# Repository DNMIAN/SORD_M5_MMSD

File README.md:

SORD m5 メモリマッパー (+SD)  

注意  
・m5 Jr.に挿せるかは検証できていません。  
・純正電源で動作するかは確認できていません。（外部電源入力は可能）  

1. 概要  
  
本ハードウェアは、SORD m5（および互換PC）に、ROMを512Kバイト、RAMを512Kバイトを拡張する装置です。  
各メモリは16Kバイト単位のセグメントに分割され、ROM32ページ、RAM32ページとして管理します。  
CPUのメモリ空間64Kバイトを16Kバイト単位で4分割し、CPU空間0～3とします。  
それぞれのCPU空間について、任意のページを対応させることができます。  
（いわゆるMSXのメモリマッパーです）  
  
また、yanatakaさんのMSX_SD ver1.6 (https://github.com/yanataka60/MSX_SD) を使用することを目的とした、  
MSXカートリッジI/F（以降、MSX-I/F)を備えています。  

2. 製作について  
  
組み立て以外に、EPROM書き込みが必要です。  
  
また、MSX_SDのドキュメントも必ず読みましょう。  
MSX_SDはArduinoスケッチ書き込みが必要です。  

3. 基板、部品リスト  
  
回路図とガーバーデータはKiCad7.0で作成しています。  
  
動作確認をした部品リストを、以下に示します。  
74HCをLSにした場合、動作しない可能性があります。  
  
U1,U2 : 74LS670 x2  
U3 : 74HC244  
U4 : HM628512ALP-7  
U5 : 512Kx8bit以下 DIP32 EPROM（M27C4001-10F1,W27C010-70で確認）  
U6 : 74HC20  
U7 : 74HC00  
U8 : 74HC30  
U9 : 74HC139  
CON : カードエッジコネクタ 2x25P 2.54mm  
C1～C9 : 積層セラミックコンデンサ 50V 0.1uF x9  
C10 : 電解コンデンサ 16V 100uF  
RN1 : 集合抵抗 6素子 10kΩ  
R1 : 抵抗 10kΩ  
SW1,SW2 : タクトスイッチ TVDP17-050B-D x2  
EX5V : ピンヘッダ 1x2P 2.54mm  
EX12V,GND : ピンヘッダ 1x3P 2.54mm  
EXIO,A4～A7 : ピンヘッダ 1x3P 2.54mm x5  
ICソケット : DIP32（U5用）  
ジャンパーピン : 2.54mm（EX5V,EXIO,A4～A7用） x6  
  
MSX_SD ver1.6 : 基板は公開されているガーバーから作成  
U1 : 74HC02  
U2 : 74HC138  
U3 : W27C512-45Z（後半32KBを使用） ※MSXで動作確認時に使用  
U4 : uPD8255AC-5  
U5 : Arduino Pro Mini 328 5V 16MHz（ピンヘッダ付属）  
J3 : MicroSD Card Adapter  
C1～C4 : 積層セラミックコンデンサ 50V 0.1uF x4  
C5 : 電解コンデンサ 16V 100uF  
D1 : ダイオード 1N4148  
ピンヘッダ : 1x2P 2.54mm（Arduino A4,A5用）  
ICソケット : DIP28（U3用）  
microSDカード : 2GB  

4. ジャンパー設定  
  
基板上にあるジャンパーついての説明です。  
EXIO,A4～A7ジャンパーは●側をショート、EX5V-5Vもショートしてください。（計6箇所）  

EXIO : MSX-I/Fの/IORQを、選択（/EXIOA or /EXIOB）します。m5は7xHを使用するので/EXIOBを設定します。  
A4～A7 : アドレスバスA4～A7を選択します（H or L）、これは使用するMSXカートリッジの仕様に強制的に合わせるものです。MSX_SDのIOポートは、38H～3BHなので、A7L, A6L, A5H, A4Hを設定します。  
EX5V : MSX-I/Fの5V供給を選択します。5Vとショートでm5から供給です。外部供給する場合、ジャンパーを外して、EX5V側へ5Vを接続します。  
5V : m5供給の5Vです。  
EX12V : MSX_SDでは使用しません。ジャンパーはしないでください。MSX-I/Fに±12Vが必要な場合は、それぞれのピンから外部供給できます。  
GND : 外部供給時のGNDを接続します。  
  
m5カートリッジバスの/IORQは、6xHアクセスで/EXIOA、7xHアクセスで/EXIOBがアサートされます。  
アドレスをそのままMSX-I/Fに出力した場合、MSXカートリッジは60H～7FHまでのIO機器しか使用できません。  
MSX_SDは38H～3BHを使用します。  
上位4bitを3(0011b)に固定することで、m5での78Hアクセスを、MSX-I/Fでは38Hアクセスに見せかけます。  
  
この仕組みを使用して、他のIOカートリッジを動作させることができるかもしれません。  
（MSX-MUSICの7CH,7DHを、6CH,6DHでアクセスするなど（メモリマッパー7CH～7FHとの競合回避））  

5. Arduinoスケッチについて  
  
MSXM5_SD.inoファイルを使用してください。  
MSX_SD.inoにm5処理を追加しているので、そのままMSXでも動作します。  

6. ROMについて  
  
メモリマッパーに実装するROMは、4Mbit(M27C4001, AM27C040, W27E040など), 2Mbit, 1Mbit等の  
32ピンDIPパッケージが使用可能です。（容量が少ない場合は、サイズ毎にページ内容がミラーされます）  
  
MSX_SD上のROMは使用しません。m5のみで使用なら実装する必要はありません。  

7. マッパーセグメントの切替について  
  
CPU空間0～3の対応は、マッパーセグメント選択レジスタによって決められます。  
マッパーセグメント選択レジスタは、I/Oアドレスの7CH番地から7FH番地までの4バイトです。  
レジスタ値は00H～1FHでROM, 20H～3FHでRAMを選択します。  
  
電源投入後の初期値は、全レジスタ値ともに不定のため、マッパーセグメント選択レジスタに書き込むまでは  
強制的に無効（全レジスタ値=00H扱い）する機能を実装しています。  
このため、ROMの0ページに適切な初期化処理を配置するのが良いでしょう。  
  
また、m5のハードウェア制約により、ページ0の0000H～1FFFHはIPLROM、ページ1の7000～7FFFHは内蔵RAMに固定されます。  
  
m5のブートシーケンスは、詳細は書きませんが、起動時に2000Hから 02 xx yy zz vv のコードがあれば、vvzzを呼び出します。  
vvzzから復帰後、yyxxを呼び出しますが、復帰しないプログラムならyyxxを設定する必要はありません。  
  
よって、ページ0の2000Hからマッパー初期化処理を配置することになります。  
しかし、実行中のコードがあるページを切り替えると、コードがすり替わってしまい想定外の動作となるため、  
別ページで切替処理を実行する必要があります。  
  
電源投入時は全ページ0となっているため、2000Hからのコードは、6000H, A000H, E000Hでもアクセスすることができます。  
これを利用して、例えばAxxxHへ分岐して、そこでページ0のマッパー設定を行うと良いように見えますが、これは間違いです。  
  
前述にある「強制的に無効」する機能は、マッパーレジスタに書き込みを行うことで、解除されます。  
よって、解除された瞬間に、不定レジスタ値でページが切り替わってしまう可能性があります。  
これを回避するため、最初はページ0のレジスタ値を0に更新します。  
その後、ページ1,2,3のレジスタ値についても適切に更新しておくのが良いでしょう。  
  
なお、「強制的に無効」する機能は、リセットでは有効になりません。  
マッパーレジスタ値も、リセットでは変化しません。  
「強制的に無効」する機能を有効にしたい（＝ページ0から実行）場合は、ボード上の「MAP Disable」ボタンを一度押してください。  
押した瞬間に動作しますので、その後、RESETボタンも押して再起動するのが良いでしょう。  
電源投入時は、（ほぼ）有効になると思いますが、起動しない場合は「MAP Disable」＋「RESET」を試して見ましょう。  

8. MSX_SD上のSDアクセスについて  
  
ハード的な仕様はオリジナルのままです。  
MSX_SDで使うSDカードは8GB以下が望ましいとの記載がありました。  
  
SDアクセス（＋マッパー切替）については、BASIC-I,BASIC-G用の簡易プログラムを作りました。  
（yanatakaさんのPC-8001_SDを参考にしています。）  
使い方は、ソースコードの先頭にあるコメントを参照してください。  
なお、SD読み書き時のエラーチェックはしていません、容量不足などには注意ください。  

9. プログラムとか  
  
MSXM5_SD.ino : MSX_SDのArduinoスケッチ  
  
EXT_ROM_M5.s : SDアクセス（＋マッパー切替） ソースコード  
EXT_ROM_M5_G.ROM : BASIC-G用のRAWファイル（6000H～6FFFHへ実装用）  
EXT_ROM_M5_I.ROM : BASIC-I用のRAWファイル（6000H～6FFFHへ実装用）  
  
BOOT_SAMPLE.s : ブート サンプルソースコード  
BOOT_SAMPLE.rom : RAWファイル（2000H～2FFFHへ実装用）  
  
BOOT_SEL.s : ブートセレクターソースコード  
BOOT_SEL.rom : RAWファイル（2000H～2FFFHへ実装用）  

10. ライセンスとか  
  
This project is licensed under the MIT License, see the LICENSE.txt file for details

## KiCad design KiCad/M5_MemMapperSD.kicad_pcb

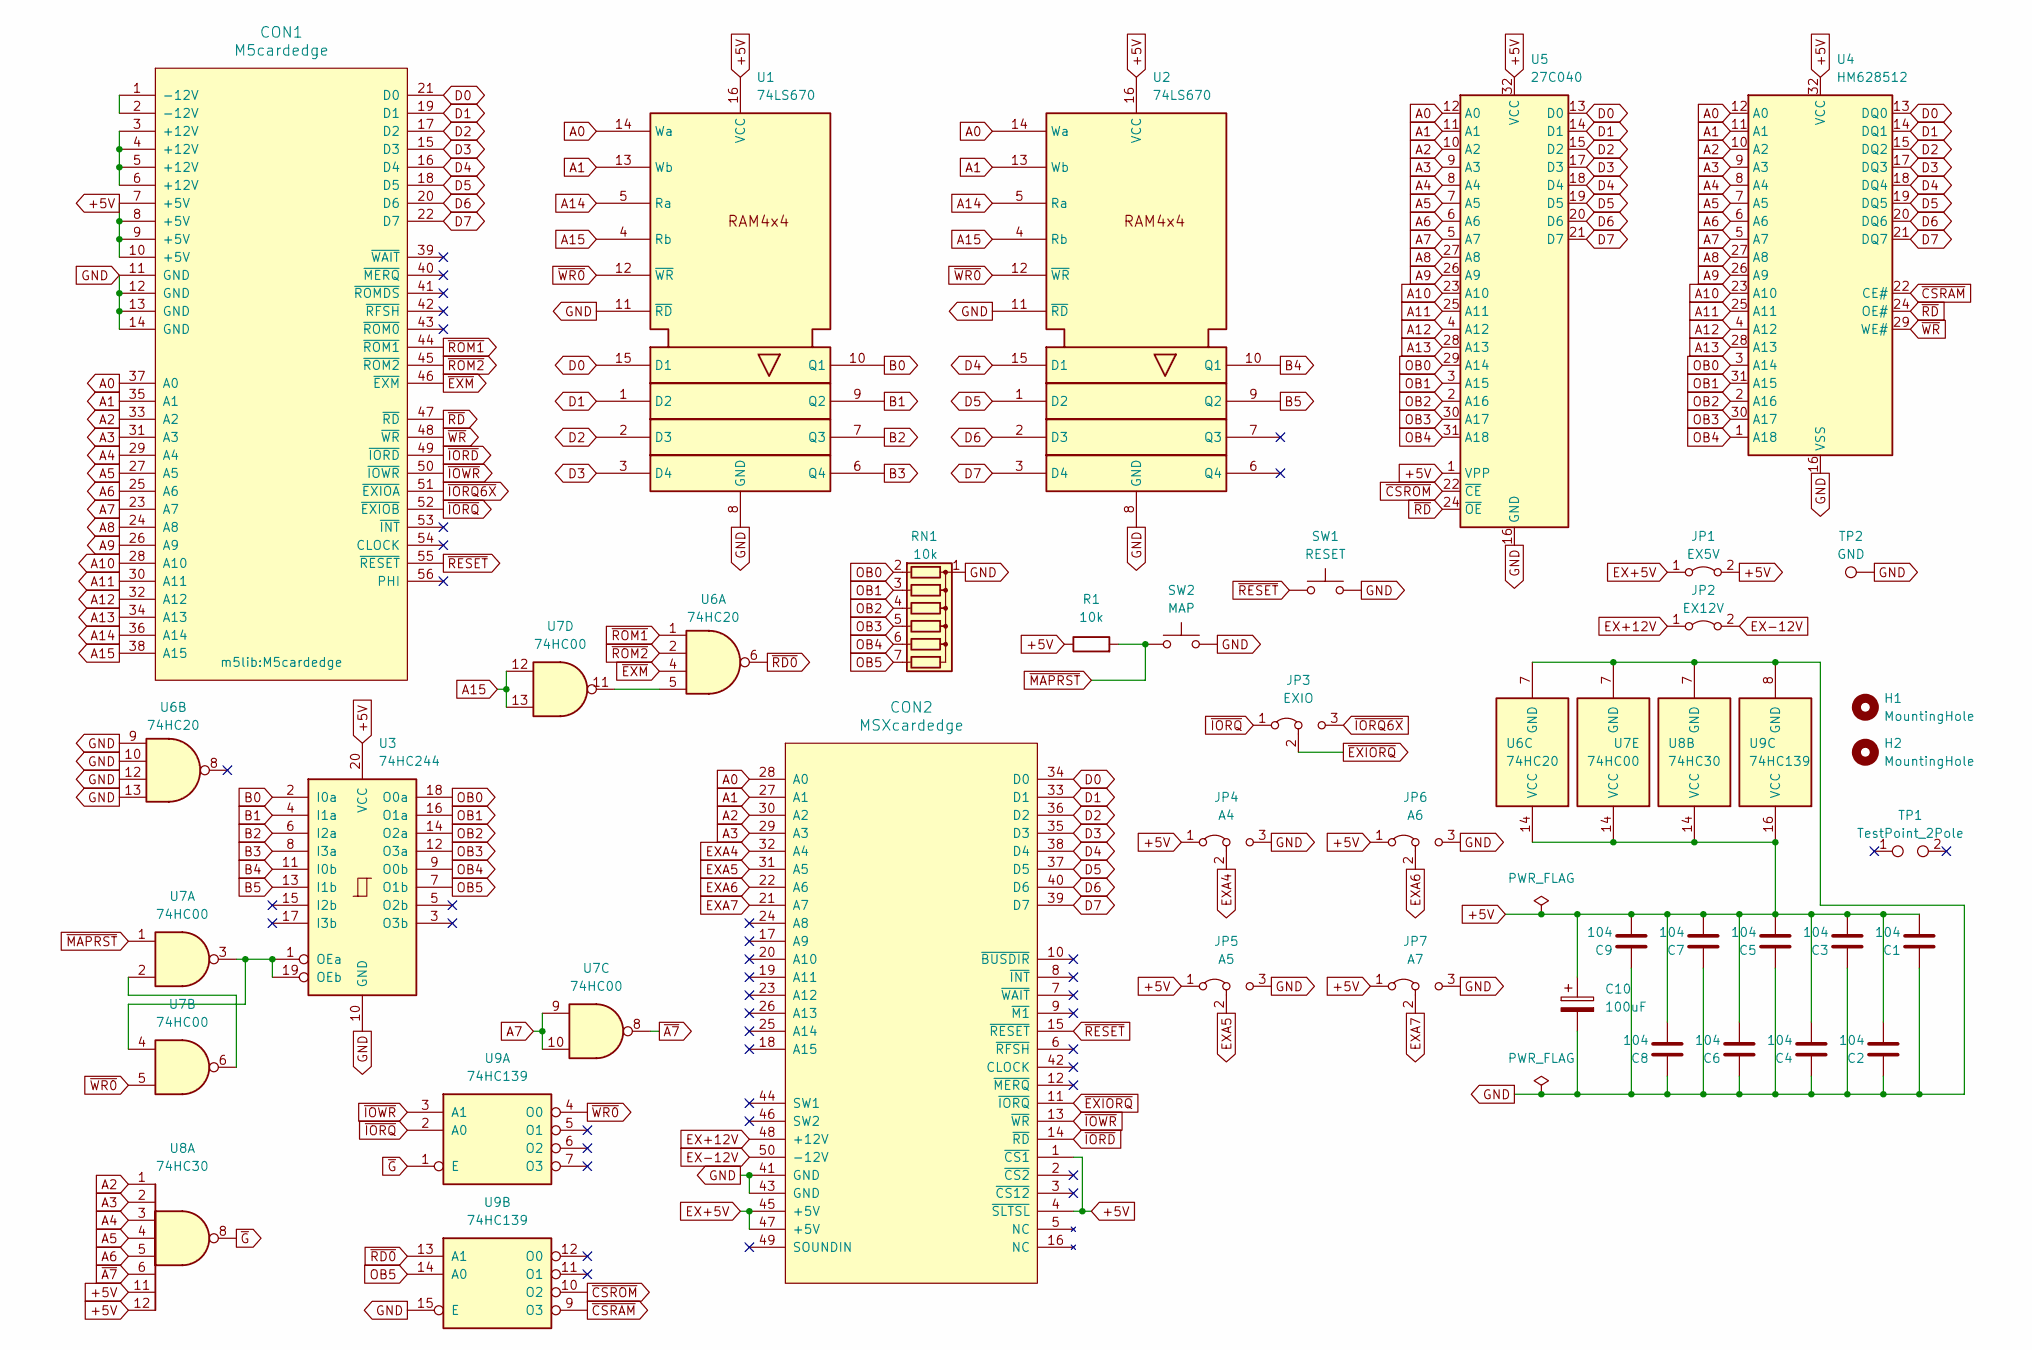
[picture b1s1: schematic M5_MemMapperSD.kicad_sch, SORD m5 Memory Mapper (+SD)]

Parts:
C1, C2, C3, C4, C5, C6, C7, C8, C9: 104; C_Disc_D5.0mm_W2.5mm_P2.50mm
C10: 100uF; CP_Radial_D5.0mm_P2.50mm
CON1: M5cardedge
CON2: MSXcardedge; 50_pin_edge_female
H1, H2: MountingHole; MountingHole_4.5mm
JP1: EX5V; PinHeader_1x02_P2.54mm_Vertical
JP2: EX12V; PinHeader_1x02_P2.54mm_Vertical
JP3: EXIO; PinHeader_1x03_P2.54mm_Vertical
JP4: A4; PinHeader_1x03_P2.54mm_Vertical
JP5: A5; PinHeader_1x03_P2.54mm_Vertical
JP6: A6; PinHeader_1x03_P2.54mm_Vertical
JP7: A7; PinHeader_1x03_P2.54mm_Vertical
R1: 10k; R_Axial_DIN0207_L6.3mm_D2.5mm_P7.62mm_Horizontal
RN1: 10k; R_Array_SIP7
SW1: RESET; SW_PUSH_6mm_H4.3mm_2pin
SW2: MAP; SW_PUSH_6mm_H4.3mm_2pin
TP1: TestPoint_2Pole; C_Disc_D5.0mm_W2.5mm_P2.50mm
TP2: GND; TestPoint_THTPad_2.0x2.0mm_Drill1.0mm
U1, U2: 74LS670; DIP-16_W7.62mm
U3: 74HC244; DIP-20_W7.62mm
U4: HM628512; DIP-32_W15.24mm
U5: 27C040; DIP-32_W15.24mm
U6: 74HC20; DIP-14_W7.62mm
U7: 74HC00; DIP-14_W7.62mm
U8: 74HC30; DIP-14_W7.62mm
U9: 74HC139; DIP-16_W7.62mm

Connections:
+5V: C1.2, C2.2, C3.2, C4.2, C5.2, C6.2, C7.2, C8.2, C9.2, C10.1, CON1.7 (+5V), CON1.8 (+5V), CON1.9 (+5V), CON1.10 (+5V), CON2.1 (~CS1), CON2.4 (~SLTSL), JP1.2 (B), JP4.1 (A), JP5.1 (A), JP6.1 (A), JP7.1 (A), R1.1, U1.16 (VCC), U2.16 (VCC), U3.20 (VCC), U4.32 (VCC), U5.1 (VPP), U5.32 (VCC), U6.14 (VCC), U7.14 (VCC), U8.11, U8.12, U8.14 (VCC), U9.16 (VCC)
A0: CON1.37 (A0), CON2.28 (A0), U1.14 (Wa), U2.14 (Wa), U4.12 (A0), U5.12 (A0)
A1: CON1.35 (A1), CON2.27 (A1), U1.13 (Wb), U2.13 (Wb), U4.11 (A1), U5.11 (A1)
A2: CON1.33 (A2), CON2.30 (A2), U4.10 (A2), U5.10 (A2), U8.1
A3: CON1.31 (A3), CON2.29 (A3), U4.9 (A3), U5.9 (A3), U8.2
A4: CON1.29 (A4), U4.8 (A4), U5.8 (A4), U8.3
A5: CON1.27 (A5), U4.7 (A5), U5.7 (A5), U8.4
A6: CON1.25 (A6), U4.6 (A6), U5.6 (A6), U8.5
A7: CON1.23 (A7), U4.5 (A7), U5.5 (A7), U7.9, U7.10
A8: CON1.24 (A8), U4.27 (A8), U5.27 (A8)
A9: CON1.26 (A9), U4.26 (A9), U5.26 (A9)
A10: CON1.28 (A10), U4.23 (A10), U5.23 (A10)
A11: CON1.30 (A11), U4.25 (A11), U5.25 (A11)
A12: CON1.32 (A12), U4.4 (A12), U5.4 (A12)
A13: CON1.34 (A13), U4.28 (A13), U5.28 (A13)
A14: CON1.36 (A14), U1.5 (Ra), U2.5 (Ra)
A15: CON1.38 (A15), U1.4 (Rb), U2.4 (Rb), U7.12, U7.13
B0: U1.10 (Q1), U3.2 (I0a)
B1: U1.9 (Q2), U3.4 (I1a)
B2: U1.7 (Q3), U3.6 (I2a)
B3: U1.6 (Q4), U3.8 (I3a)
B4: U2.10 (Q1), U3.11 (I0b)
B5: U2.9 (Q2), U3.13 (I1b)
D0: CON1.21 (D0), CON2.34 (D0), U1.15 (D1), U4.13 (DQ0), U5.13 (D0)
D1: CON1.19 (D1), CON2.33 (D1), U1.1 (D2), U4.14 (DQ1), U5.14 (D1)
D2: CON1.17 (D2), CON2.36 (D2), U1.2 (D3), U4.15 (DQ2), U5.15 (D2)
D3: CON1.15 (D3), CON2.35 (D3), U1.3 (D4), U4.17 (DQ3), U5.17 (D3)
D4: CON1.16 (D4), CON2.38 (D4), U2.15 (D1), U4.18 (DQ4), U5.18 (D4)
D5: CON1.18 (D5), CON2.37 (D5), U2.1 (D2), U4.19 (DQ5), U5.19 (D5)
D6: CON1.20 (D6), CON2.40 (D6), U2.2 (D3), U4.20 (DQ6), U5.20 (D6)
D7: CON1.22 (D7), CON2.39 (D7), U2.3 (D4), U4.21 (DQ7), U5.21 (D7)
EX+5V: CON2.45 (+5V), CON2.47 (+5V), JP1.1 (A)
EX+12V: CON2.48 (+12V), JP2.1 (A)
EX-12V: CON2.50 (-12V), JP2.2 (B)
EXA4: CON2.32 (A4), JP4.2 (C)
EXA5: CON2.31 (A5), JP5.2 (C)
EXA6: CON2.22 (A6), JP6.2 (C)
EXA7: CON2.21 (A7), JP7.2 (C)
unnamed: CON1.3 (+12V), CON1.4 (+12V), CON1.5 (+12V), CON1.6 (+12V)
unnamed: CON1.1 (-12V), CON1.2 (-12V)
unnamed: U3.1 (OEa), U3.19 (OEb), U7.3, U7.4
unnamed: U6.5, U7.11
unnamed: U7.2, U7.6
OB0: RN1.2 (R1), U3.18 (O0a), U4.3 (A14), U5.29 (A14)
OB1: RN1.3 (R2), U3.16 (O1a), U4.31 (A15), U5.3 (A15)
OB2: RN1.4 (R3), U3.14 (O2a), U4.2 (A16), U5.2 (A16)
OB3: RN1.5 (R4), U3.12 (O3a), U4.30 (A17), U5.30 (A17)
OB4: RN1.6 (R5), U3.9 (O0b), U4.1 (A18), U5.31 (A18)
OB5: RN1.7 (R6), U3.7 (O1b), U9.14 (A0)
~A7: U7.8, U8.6
~CSRAM: U4.22 (CE#), U9.9 (O3)
~CSROM: U5.22 (~CE), U9.10 (O2)
~EXIORQ: CON2.11 (~IORQ), JP3.2 (C)
~EXM: CON1.46 (~EXM), U6.4
~G: U8.8, U9.1 (E)
~IORD: CON1.49 (~IORD), CON2.14 (~RD)
~IORQ6X: CON1.51 (~EXIOA), JP3.3 (B)
~IORQ: CON1.52 (~EXIOB), JP3.1 (A), U9.2 (A0)
~IOWR: CON1.50 (~IOWR), CON2.13 (~WR), U9.3 (A1)
~RD0: U6.6, U9.13 (A1)
~RD: CON1.47 (~RD), U4.24 (OE#), U5.24 (~OE)
~ROM1: CON1.44 (~ROM1), U6.1
~ROM2: CON1.45 (~ROM2), U6.2
~WR0: U1.12 (~WR), U2.12 (~WR), U7.5, U9.4 (O0)
~WR: CON1.48 (~WR), U4.29 (WE#)

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
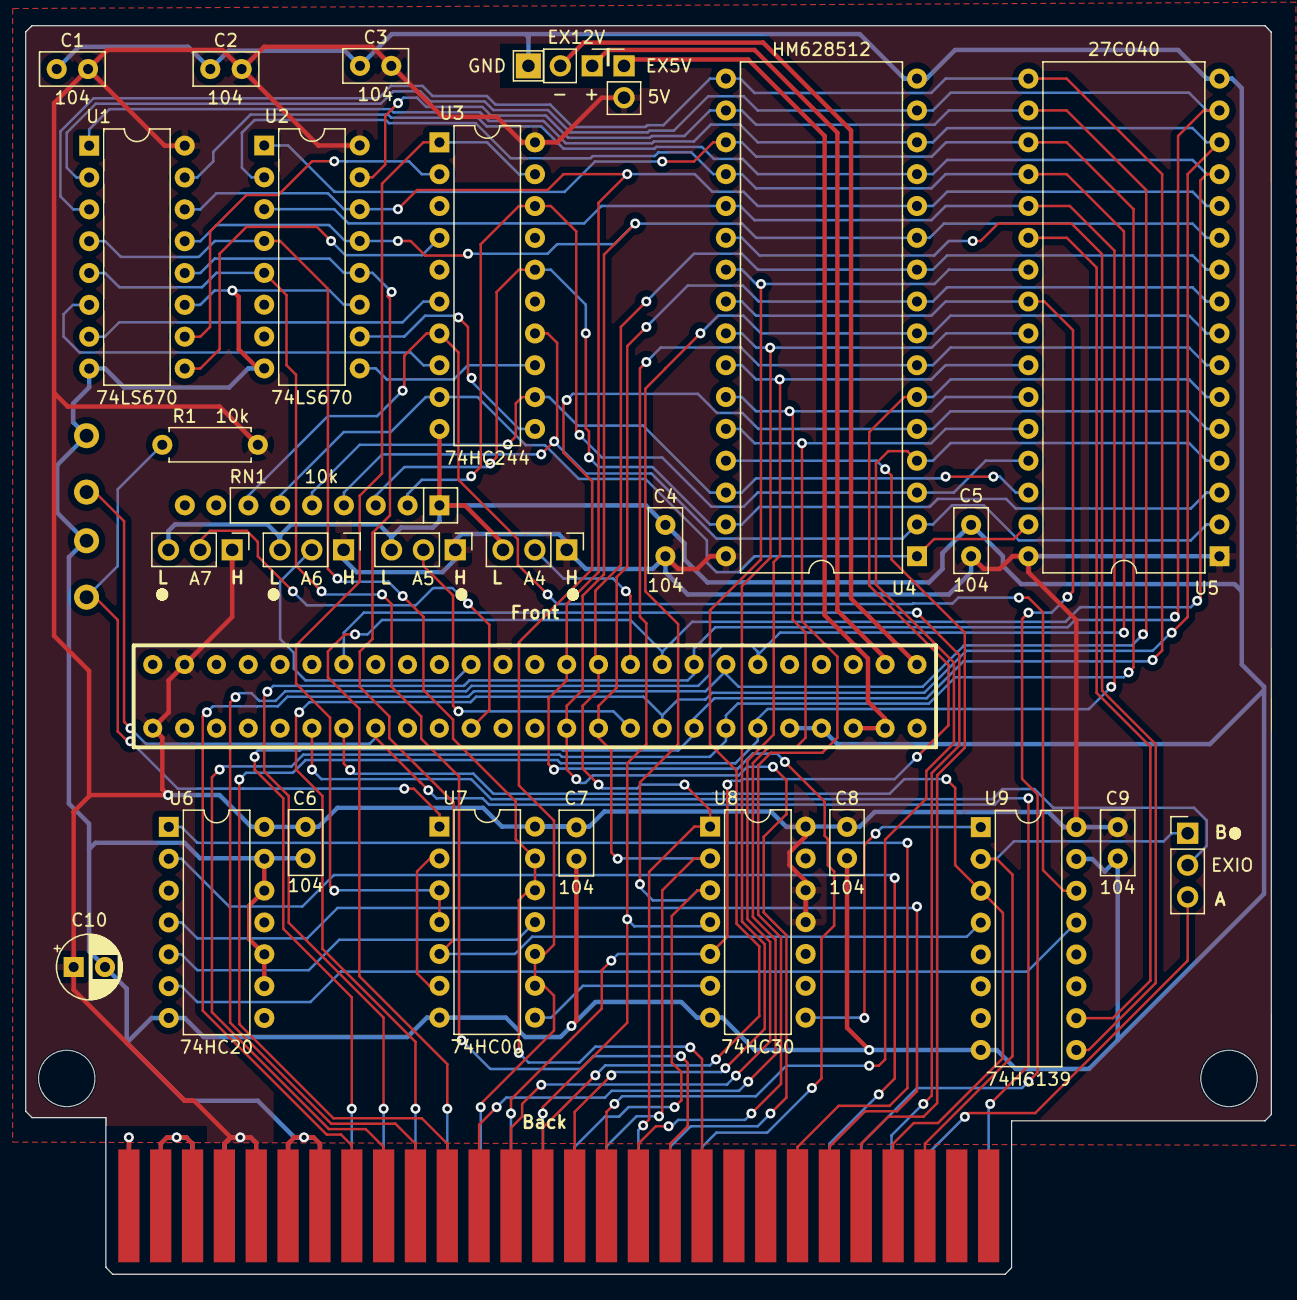
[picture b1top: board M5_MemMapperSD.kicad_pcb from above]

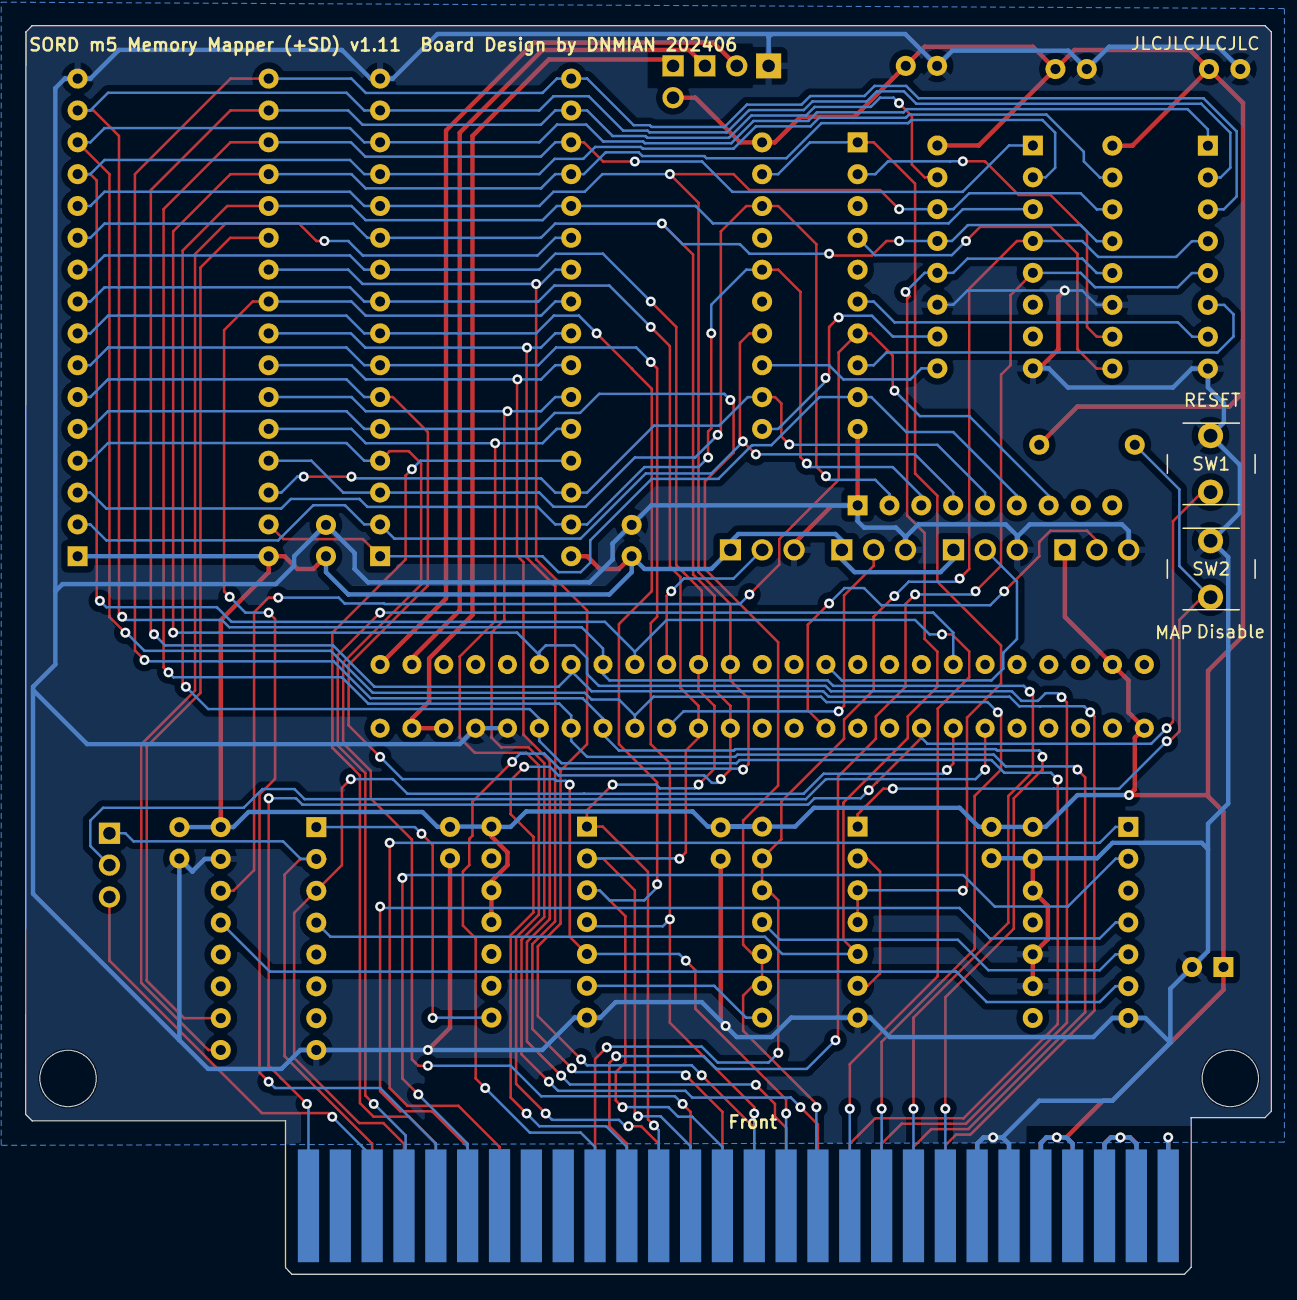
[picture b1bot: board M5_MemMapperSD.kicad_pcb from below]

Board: 2 copper layers, 99.4 x 99.6 mm, 36 parts (2 on the bottom side), 68 nets.
